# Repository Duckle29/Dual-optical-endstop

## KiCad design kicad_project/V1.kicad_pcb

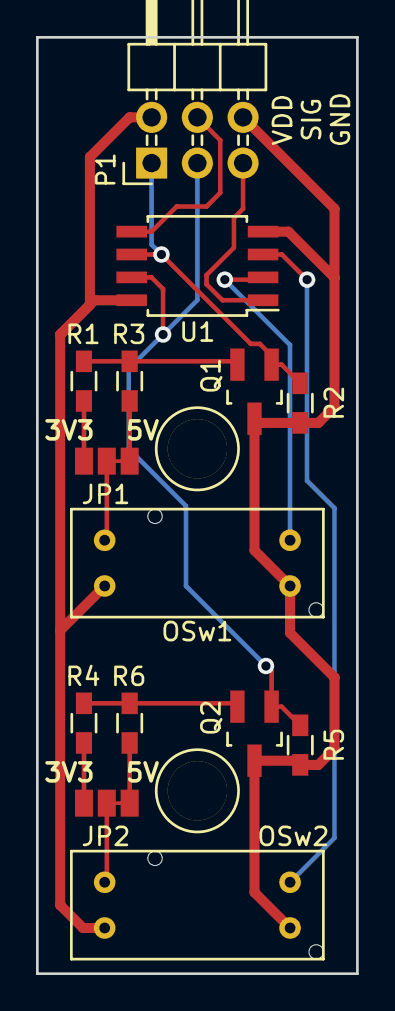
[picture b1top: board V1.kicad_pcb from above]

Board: 2 copper layers, 17.8 x 52.0 mm, 14 parts (0 on the bottom side), 16 nets.

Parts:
JP1, JP2: JUMPER3; Solder-jumper-12NC-23NO
OSw1, OSw2: ITR9606
P1: CONN_02X03; Pin_Header_Angled_2x03
Q1, Q2: FDN339AN; SOT-23_Handsoldering
R1, R4: 47R; R_0603_HandSoldering
R2, R5: 10K; R_0603_HandSoldering
R3, R6: 100R; R_0603_HandSoldering
U1: ATTINY85-S; SOIJ-8_5.3x5.3mm_Pitch1.27mm

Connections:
GND: OSw1.4, OSw2.4, P1.6, Q1.3, Q2.3, R2.2, R5.2, U1.4
MISO: P1.1, Q1.1, R2.1, U1.6
MOSI: P1.4, U1.5
unnamed: JP1.1, R3.1
unnamed: JP1.2, OSw1.2
unnamed: JP1.3, R1.1
unnamed: JP2.1, R6.1
unnamed: JP2.2, OSw2.2
unnamed: JP2.3, R4.1
unnamed: Q1.2, R1.2, R3.2
unnamed: Q2.2, R4.2, R6.2
SCK: P1.3, Q2.1, R5.1, U1.7
SW1: OSw1.3, U1.2
SW2: OSw2.3, U1.3
VDD: OSw1.1, OSw2.1, P1.2, U1.8
~Reset: P1.5, U1.1

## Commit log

2016-09-09 Added dimentions to board
